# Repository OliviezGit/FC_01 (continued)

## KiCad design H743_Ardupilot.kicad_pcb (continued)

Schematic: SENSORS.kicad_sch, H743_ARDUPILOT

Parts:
C44, C45, C46: 4.7u; C_0402_1005Metric; MPN CL05A475MP5NRNC; DigiKey Part Number 1276-1482-1-ND
C47, C48, C49, C50, C51, C52: 100n X7R; C_0402_1005Metric; MPN CL05B104KO5NNNC; DigiKey Part Number 1276-1001-1-ND
C53, C54, C55, C56: 100n; C_0402_1005Metric; MPN CL05B104KO5NNNC; DigiKey Part Number 1276-1001-1-ND
J8: I2C1; SolderPadArray_1x04_P2.54mm_1x1mm; DigiKey Status Element PCB; aucun composant achete
J9: I2C_2; SolderPadArray_1x04_P2.54mm_1x1mm; DigiKey Status Element PCB; aucun composant achete
R34, R35, R36: 0R; R_0402_1005Metric; MPN RC0402JR-070RL; DigiKey Specs 0 Ω jumper, 0402 (1005), thick film
R37, R38: 4.7K; R_0402_1005Metric; MPN RC0402FR-074K7L; DigiKey Specs 4.7 kΩ ±1%, 0.063 W, 0402
U9: BMI088; BMI088_LGA16_4.5x3mm; MPN BMI088; DigiKey Specs 6-axis accel + gyro, I2C/SPI, LGA-16 4.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
U10: LSM6DSV16X; LSM6DSV16X_LGA14_3x2.5mm; MPN LSM6DSV16XTR; DigiKey Part Number 497-LSM6DSV16XTRCT-ND
U11: ICM-45686; TDK_ICM45686_LGA14_3x2.5mm; MPN ICM-45686; DigiKey Product ID 24374985
U12: BMP581; QFN10_BMP581_BOS; MPN BMP581; DigiKey Part Number 828-BMP581CT-ND
U13: DPS368XTSA1; Infineon_DPS368_PG-VLGA-8-2; MPN DPS368XTSA1; LCSC Part C3232508

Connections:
+3V3_MCU: C50.1, C51.1, C52.1, C53.1, C54.1, R37.1, R38.1, U9.11 (VDDIO), U10.5 (VDDIO), U11.5 (VDDIO), U12.1 (VDDIO), U13.2 (CSB), U13.6 (VDDIO); also elsewhere on the board
+3V3_SENS: C44.1, C45.1, C46.1, C47.1, C48.1, C49.1, C55.1, C56.1, U9.3 (VDD), U10.8 (VDD), U11.8 (VDD), U12.10 (VDD), U13.8 (VDD); also elsewhere on the board
+5V_SYS: J8.1, J9.1; also elsewhere on the board
/MCU/I2C1.SCL: J8.4; also elsewhere on the board
/MCU/I2C1.SDA: J8.3; also elsewhere on the board
/MCU/I2C2.SCL: J9.4, R37.2, U13.4 (SCL); also elsewhere on the board
/MCU/I2C2.SDA: J9.3, R38.2, U13.3 (SDA); also elsewhere on the board
/MCU/IMU1_CLKIN: R35.1; also elsewhere on the board
/MCU/IMU1_DRDY: R34.1; also elsewhere on the board
/MCU/IMU2_DRDY: R36.2; also elsewhere on the board
/MCU/IMU3_A_CS: U9.14 (~CSB1); also elsewhere on the board
/MCU/IMU3_G_CS: U9.5 (~CSB2); also elsewhere on the board
/MCU/SPI1.CS: U11.12 (CS); also elsewhere on the board
/MCU/SPI1.MISO: U11.1 (SDO/AD0); also elsewhere on the board
/MCU/SPI1.MOSI: U11.14 (SDI/SDIO/SDA); also elsewhere on the board
/MCU/SPI1.SCLK: U11.13 (SCLK/SCL); also elsewhere on the board
/MCU/SPI2.CS: U12.6 (CSB); also elsewhere on the board
/MCU/SPI2.MISO: U12.5 (SDO); also elsewhere on the board
/MCU/SPI2.MOSI: U12.4 (SDI); also elsewhere on the board
/MCU/SPI2.SCLK: U12.2 (SCK); also elsewhere on the board
/MCU/SPI3.MISO: U9.10 (SDO2), U9.15 (SDO1); also elsewhere on the board
/MCU/SPI3.MOSI: U9.9 (SDI/SDA); also elsewhere on the board
/MCU/SPI3.SCLK: U9.8 (SCK/SCL); also elsewhere on the board
/MCU/SPI4.CS: U10.12 (CS); also elsewhere on the board
/MCU/SPI4.MISO: U10.1 (SDO/SA0); also elsewhere on the board
/MCU/SPI4.MOSI: U10.14 (SDA); also elsewhere on the board
/MCU/SPI4.SCLK: U10.13 (SCL); also elsewhere on the board
GND: C44.2, C45.2, C46.2, C47.2, C48.2, C49.2, C50.2, C51.2, C52.2, C53.2, C54.2, C55.2, C56.2, J8.2, J9.2, U9.2 (GNDA), U9.4 (GNDA), U9.6 (GNDIO), U9.7 (PS), U10.2 (SDx/AH1/Qvar1), U10.3 (SCx/AH2/Qvar2), U10.6 (GND), U10.7 (GND), U11.6 (GND), U12.3 (VSS), U12.7 (INT), U12.8 (VSS), U12.9 (VSS), U13.1 (GND), U13.7 (GND); also elsewhere on the board
unnamed: R36.1, U10.4 (INT1)
unnamed: R34.2, U11.4 (INT1)
unnamed: R35.2, U11.9 (INT2/FSYNC/CLKIN)

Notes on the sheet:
I2C_1
I2C_2

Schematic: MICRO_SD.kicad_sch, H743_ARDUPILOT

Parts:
C57: 1u; C_0402_1005Metric; MPN CL05A105KA5NQNC; DigiKey Part Number 1276-1445-1-ND
C58: 100n; C_0402_1005Metric; MPN CL05B104KO5NNNC; DigiKey Part Number 1276-1001-1-ND
J12: 10067099-200LF; Amphenol_10067099-200LF_RevH; MPN 10067099-200LF; LCSC Part C5408015
R41, R42, R43, R44, R45, R46: 10K; R_0402_1005Metric; MPN RC0402FR-0710KL; DigiKey Specs 10K ±1%, 0402 (1005), thick film

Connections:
+3V3_MCU: C57.1, C58.1, J12.4 (VDD), R41.2, R42.2, R43.2, R44.2, R45.2, R46.2; also elsewhere on the board
/MCU/SDIO.CK: J12.5 (CLK), R41.1; also elsewhere on the board
/MCU/SDIO.CMD: J12.3 (CMD), R42.1; also elsewhere on the board
/MCU/SDIO.D0: J12.7 (DAT0), R43.1; also elsewhere on the board
/MCU/SDIO.D1: J12.8 (DAT1), R44.1; also elsewhere on the board
/MCU/SDIO.D2: J12.1 (DAT2), R45.1; also elsewhere on the board
/MCU/SDIO.D3: J12.2 (DAT3/CD), R46.1; also elsewhere on the board
GND: C57.2, C58.2, J12.6 (VSS), J12.9 (CD1), J12.10 (CD2); also elsewhere on the board

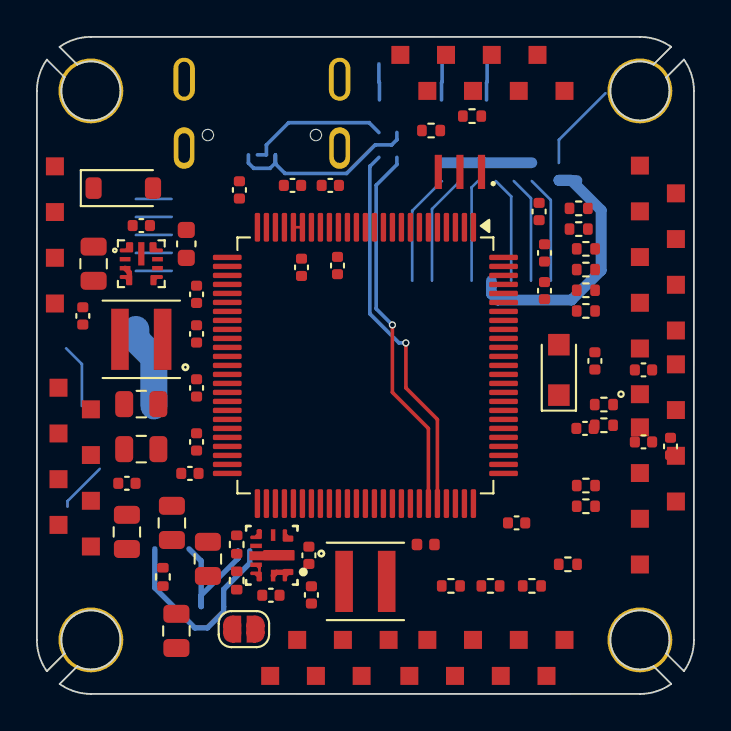
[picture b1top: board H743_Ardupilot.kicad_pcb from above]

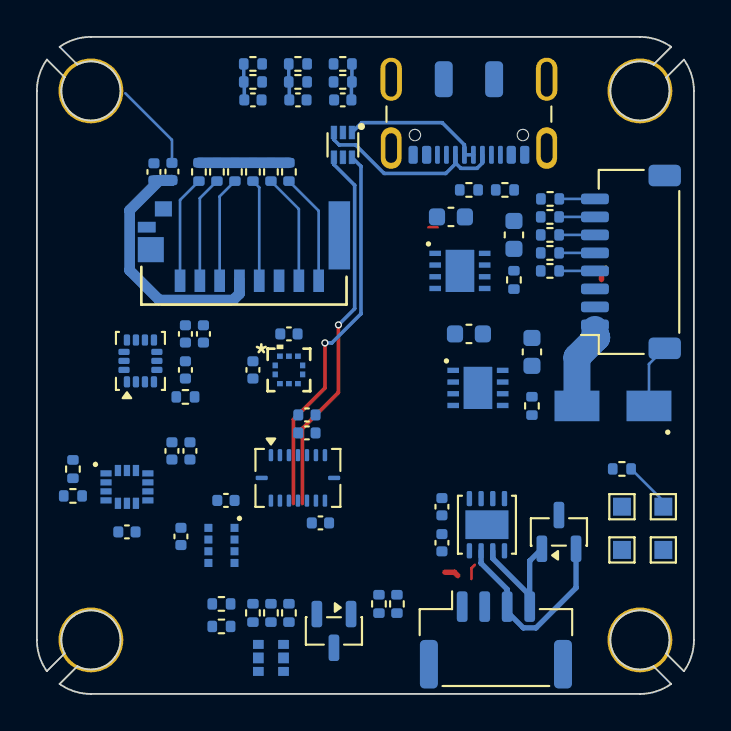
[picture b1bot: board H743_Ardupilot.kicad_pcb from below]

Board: 6 copper layers, 36.5 x 36.5 mm, 156 parts (77 on the bottom side), 123 nets.

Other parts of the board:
C18, C37: 10u; C_0805_2012Metric
C19, C22: 100n; C_0402_1005Metric
C26: 22u; C_0805_2012Metric
L2: 3.3u; L_Coilcraft_XGL4030
R8, R10: 100K; R_0402_1005Metric
R9: 16.5k; R_0402_1005Metric
R11: 12.4K; R_0402_1005Metric
U4: LMR604303SRAKRQ1; TI_RAK0009A_WQFN-HR-9_2.5x2.0mm

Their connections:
+9V: C26.1, C37.1, L2.2, R8.2, R10.2; also elsewhere on the board
/POWER/SW_9V: C22.2, L2.1, U4.3 (SW)
GND: C18.2, C19.2, C26.2, C37.2, R9.1, R11.2, U4.2 (PGND); also elsewhere on the board
unnamed: C22.1, U4.4 (BOOT)
unnamed: R10.1, R11.1, U4.6 (FB)
unnamed: R9.2, U4.7 (MODE/SYNC), U4.8 (RT)
unnamed: R8.1, U4.5 (PG)
VBAT: C18.1, C19.1, U4.1 (VIN), U4.9 (EN); also elsewhere on the board

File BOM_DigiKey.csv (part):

Sheet,Reference,Value,Manufacturer,MPN,Package,Footprint,Datasheet,DigiKey_Part_Number,DigiKey_URL,DigiKey_Specs,Unit_Price_EUR,Price_Qty,Price_Checked,DigiKey_Status,Footprint_Audit,Library_Audit,Supplier,Supplier_Order_Code,Supplier_URL
MCU.kicad_sch,C1,4.7u,Samsung Electro-Mechanics,CL05A475MP5NRNC,0402 (1005),Capacitor_SMD:C_0402_1005Metric,${KIPRJMOD}/composants/pdf/CL05A475MP5NRN.pdf,1276-1482-1-ND,https://www.digikey.fr/en/products/detail/samsung-electro-me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,"4.7 µF ±20%, 10 V, X5R, 0402",0.09,1,2026-09-27,Stock 0,Voir composants/catalogue.json et verification/REPORT.md,Voir composants/README.md,DigiKey France,1276-1482-1-ND,https://www.digikey.fr/en/products/detail/samsung-electro-me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
MCU.kicad_sch,C2,100n,Samsung Electro-Mechanics,CL05B104KO5NNNC,0402 (1005),Capacitor_SMD:C_0402_1005Metric,${KIPRJMOD}/composants/pdf/CL05B104KO5NNN.pdf,1276-1001-1-ND,https://www.digikey.fr/fr/products/detail/samsung-electro-me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,"100 nF ±10%, 16 V, X7R, 0402",0.09,1,2026-09-27,Stock 103052,Voir composants/catalogue.json et verification/REPORT.md,Voir composants/README.md,DigiKey France,1276-1001-1-ND,https://www.digikey.fr/fr/products/detail/samsung-electro-me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
MCU.kicad_sch,C3,100n,Samsung Electro-Mechanics,CL05B104KO5NNNC,0402 (1005),Capacitor_SMD:C_0402_1005Metric,${KIPRJMOD}/composants/pdf/CL05B104KO5NNN.pdf,1276-1001-1-ND,https://www.digikey.fr/fr/products/detail/samsung-electro-me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,"100 nF ±10%, 16 V, X7R, 0402",0.09,1,2026-09-27,Stock 103052,Voir composants/catalogue.json et verification/REPORT.md,Voir composants/README.md,DigiKey France,1276-1001-1-ND,https://www.digikey.fr/fr/products/detail/samsung-electro-me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
MCU.kicad_sch,C4,100n,Samsung Electro-Mechanics,CL05B104KO5NNNC,0402 (1005),Capacitor_SMD:C_0402_1005Metric,${KIPRJMOD}/composants/pdf/CL05B104KO5NNN.pdf,1276-1001-1-ND,https://www.digikey.fr/fr/products/detail/samsung-electro-me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,"100 nF ±10%, 16 V, X7R, 0402",0.09,1,2026-09-27,Stock 103052,Voir composants/catalogue.json et verification/REPORT.md,Voir composants/README.md,DigiKey France,1276-1001-1-ND,https://www.digikey.fr/fr/products/detail/samsung-electro-me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
MCU.kicad_sch,C5,100n,Samsung Electro-Mechanics,CL05B104KO5NNNC,0402 (1005),Capacitor_SMD:C_0402_1005Metric,${KIPRJMOD}/composants/pdf/CL05B104KO5NNN.pdf,1276-1001-1-ND,https://www.digikey.fr/fr/products/detail/samsung-electro-me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,"100 nF ±10%, 16 V, X7R, 0402",0.09,1,2026-09-27,Stock 103052,Voir composants/catalogue.json et verification/REPORT.md,Voir composants/README.md,DigiKey France,1276-1001-1-ND,https://www.digikey.fr/fr/products/detail/samsung-electro-me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
MCU.kicad_sch,C6,100n,Samsung Electro-Mechanics,CL05B104KO5NNNC,0402 (1005),Capacitor_SMD:C_0402_1005Metric,${KIPRJMOD}/composants/pdf/CL05B104KO5NNN.pdf,1276-1001-1-ND,https://www.digikey.fr/fr/products/detail/samsung-electro-me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,"100 nF ±10%, 16 V, X7R, 0402",0.09,1,2026-09-27,Stock 103052,Voir composants/catalogue.json et verification/REPORT.md,Voir composants/README.md,DigiKey France,1276-1001-1-ND,https://www.digikey.fr/fr/products/detail/samsung-electro-me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
MCU.kicad_sch,C7,2.2u,TDK,C1005X5R1C225M050BC,0402 (1005),Capacitor_SMD:C_0402_1005Metric,${KIPRJMOD}/composants/pdf/TDK_C.pdf,,,"2.2 µF ±20%, 16 V, X5R, 0402",0.104,10,2026-09-27,Voir composants/BOM_FR.csv,Voir composants/catalogue.json et verification/REPORT.md,Voir composants/README.md,Farnell France,2525017,https://fr.farnell.com/tdk/c1005x5r1c225m050bc/condensateur-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
MCU.kicad_sch,C8,100n,Samsung Electro-Mechanics,CL05B104KO5NNNC,0402 (1005),Capacitor_SMD:C_0402_1005Metric,${KIPRJMOD}/composants/pdf/CL05B104KO5NNN.pdf,1276-1001-1-ND,https://www.digikey.fr/fr/products/detail/samsung-electro-me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,"100 nF ±10%, 16 V, X7R, 0402",0.09,1,2026-09-27,Stock 103052,Voir composants/catalogue.json et verification/REPORT.md,Voir composants/README.md,DigiKey France,1276-1001-1-ND,https://www.digikey.fr/fr/products/detail/samsung-electro-me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
MCU.kicad_sch,C9,100n,Samsung Electro-Mechanics,CL05B104KO5NNNC,0402 (1005),Capacitor_SMD:C_0402_1005Metric,${KIPRJMOD}/composants/pdf/CL05B104KO5NNN.pdf,1276-1001-1-ND,https://www.digikey.fr/fr/products/detail/samsung-electro-me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,"100 nF ±10%, 16 V, X7R, 0402",0.09,1,2026-09-27,Stock 103052,Voir composants/catalogue.json et verification/REPORT.md,Voir composants/README.md,DigiKey France,1276-1001-1-ND,https://www.digikey.fr/fr/products/detail/samsung-electro-me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
MCU.kicad_sch,C10,2.2u,TDK,C1005X5R1C225M050BC,0402 (1005),Capacitor_SMD:C_0402_1005Metric,${KIPRJMOD}/composants/pdf/TDK_C.pdf,,,"2.2 µF ±20%, 16 V, X5R, 0402",0.104,10,2026-09-27,Voir composants/BOM_FR.csv,Voir composants/catalogue.json et verification/REPORT.md,Voir composants/README.md,Farnell France,2525017,https://fr.farnell.com/tdk/c1005x5r1c225m050bc/condensateur-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
MCU.kicad_sch,C11,100n,Samsung Electro-Mechanics,CL05B104KO5NNNC,0402 (1005),Capacitor_SMD:C_0402_1005Metric,${KIPRJMOD}/composants/pdf/CL05B104KO5NNN.pdf,1276-1001-1-ND,https://www.digikey.fr/fr/products/detail/samsung-electro-me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,"100 nF ±10%, 16 V, X7R, 0402",0.09,1,2026-09-27,Stock 103052,Voir composants/catalogue.json et verification/REPORT.md,Voir composants/README.md,DigiKey France,1276-1001-1-ND,https://www.digikey.fr/fr/products/detail/samsung-electro-me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
MCU.kicad_sch,C12,100n,Samsung Electro-Mechanics,CL05B104KO5NNNC,0402 (1005),Capacitor_SMD:C_0402_1005Metric,${KIPRJMOD}/composants/pdf/CL05B104KO5NNN.pdf,1276-1001-1-ND,https://www.digikey.fr/fr/products/detail/samsung-electro-me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,"100 nF ±10%, 16 V, X7R, 0402",0.09,1,2026-09-27,Stock 103052,Voir composants/catalogue.json et verification/REPORT.md,Voir composants/README.md,DigiKey France,1276-1001-1-ND,https://www.digikey.fr/fr/products/detail/samsung-electro-me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
MCU.kicad_sch,C14,1u,Samsung Electro-Mechanics,CL05A105KA5NQNC,0402 (1005),Capacitor_SMD:C_0402_1005Metric,${KIPRJMOD}/composants/pdf/CL05A105KA5NQN.pdf,1276-1445-1-ND,https://www.digikey.fr/fr/products/detail/samsung-electro-me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,"1 µF ±10%, 25 V, X5R, 0402",0.16,1,2026-09-27,Stock 2318576,Voir composants/catalogue.json et verification/REPORT.md,Voir composants/README.md,DigiKey France,1276-1445-1-ND,https://www.digikey.fr/fr/products/detail/samsung-electro-me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
MCU.kicad_sch,C15,100n,Samsung Electro-Mechanics,CL05B104KO5NNNC,0402 (1005),Capacitor_SMD:C_0402_1005Metric,${KIPRJMOD}/composants/pdf/CL05B104KO5NNN.pdf,1276-1001-1-ND,https://www.digikey.fr/fr/products/detail/samsung-electro-me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,"100 nF ±10%, 16 V, X7R, 0402",0.09,1,2026-09-27,Stock 103052,Voir composants/catalogue.json et verification/REPORT.md,Voir composants/README.md,DigiKey France,1276-1001-1-ND,https://www.digikey.fr/fr/products/detail/samsung-electro-me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
POWER.kicad_sch,C16,10u,Murata Electronics,GRM21BR61H106KE43L,0805 (2012),Capacitor_SMD:C_0805_2012Metric,${KIPRJMOD}/composants/pdf/GRM21.pdf,490-18663-1-ND,https://www.digikey.fr/en/products/detail/murata-electronics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,"10 µF ±10%, 50 V, X5R, 0805",0.28,1,2026-09-27,Stock 0,Voir composants/catalogue.json et verification/REPORT.md,Voir composants/README.md,DigiKey France,490-18663-1-ND,https://www.digikey.fr/en/products/detail/murata-electronics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
POWER.kicad_sch,C17,100n,Murata Electronics,GCM155R71H104KE02D,0402 (1005 Metric),Capacitor_SMD:C_0402_1005Metric,${KIPRJMOD}/composants/pdf/GCM155.pdf,490-10672-1-ND,https://www.digikey.fr/fr/products/detail/murata-electronics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,"100 nF ±10%, 50 V, X7R, 0402 (1005)",0.09,1,2026-09-27,Stock 16172272,Voir composants/catalogue.json et verification/REPORT.md,Voir composants/README.md,DigiKey France,490-10672-1-ND,https://www.digikey.fr/fr/products/detail/murata-electronics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
POWER.kicad_sch,C18,10u,Murata Electronics,GRM21BR61H106KE43L,0805 (2012),Capacitor_SMD:C_0805_2012Metric,${KIPRJMOD}/composants/pdf/GRM21.pdf,490-18663-1-ND,https://www.digikey.fr/en/products/detail/murata-electronics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,"10 µF ±10%, 50 V, X5R, 0805",0.28,1,2026-09-27,Stock 0,Voir composants/catalogue.json et verification/REPORT.md,Voir composants/README.md,DigiKey France,490-18663-1-ND,https://www.digikey.fr/en/products/detail/murata-electronics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

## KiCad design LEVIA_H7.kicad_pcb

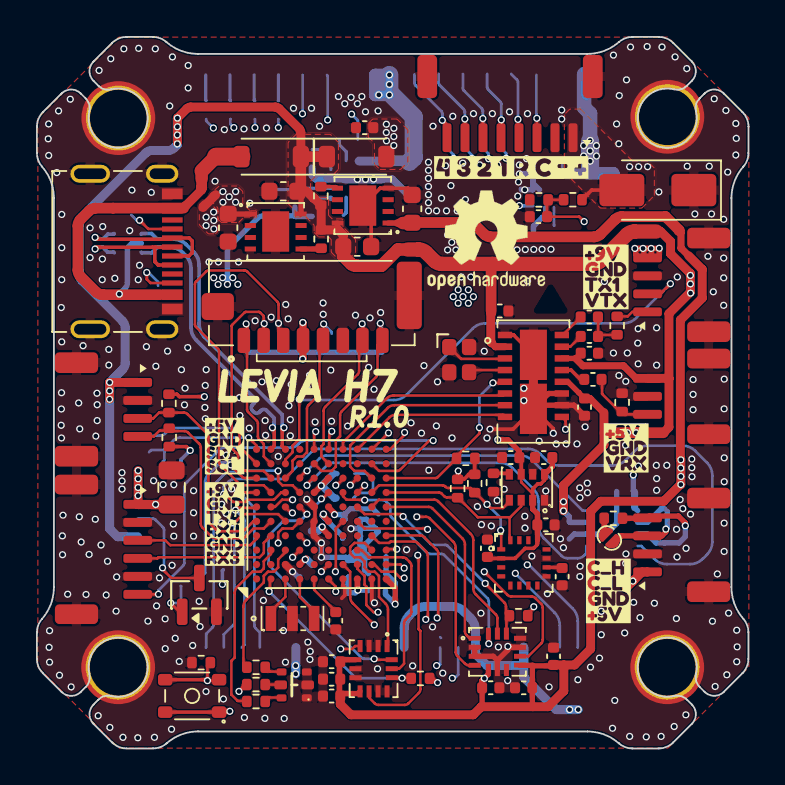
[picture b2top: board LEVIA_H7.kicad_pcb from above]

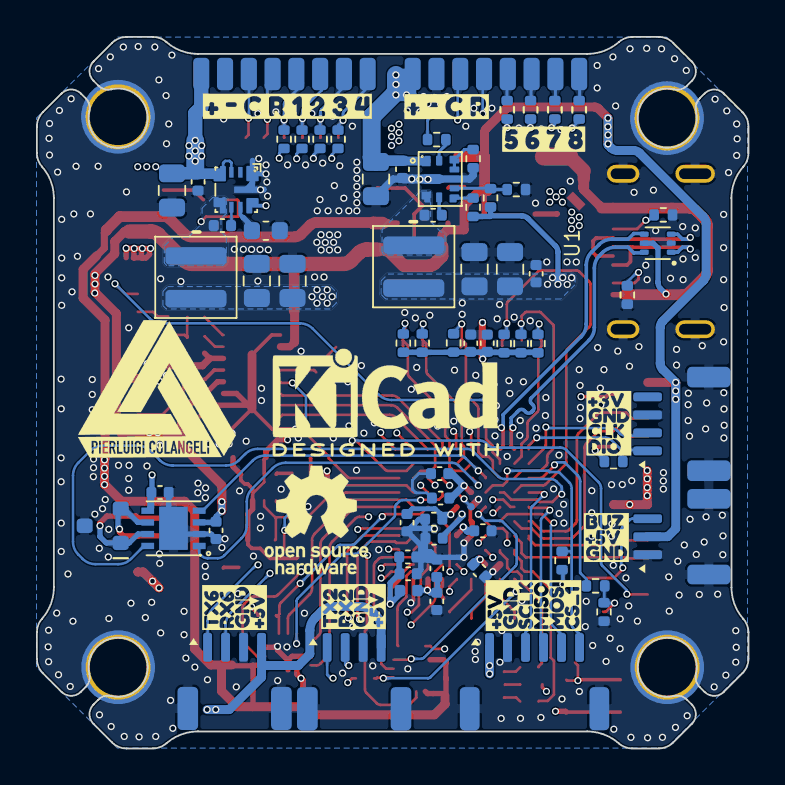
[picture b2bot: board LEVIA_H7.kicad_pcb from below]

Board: 6 copper layers, 39.5 x 39.5 mm, 170 parts (90 on the bottom side), 119 nets.

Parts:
C1, C4, C5, C6, C9, C10, C15, C16, C17, C20, C21, C26, C28, C33, C34, C35, C38, C39, C40, C43, C44, C47, C48, C49, C50, C54: 100n; C_0402_1005Metric
C2, C12, C41, C42, C51: 4.7u; C_0402_1005Metric
C3, C7, C53: 1u; C_0402_1005Metric
C8, C11: 2.2u; C_0402_1005Metric
C13, C14: 10u; C_0805_2012Metric
C18: 1u; C_0603_1608Metric
C22, C24, C25, C27, C52: 22u; C_0805_2012Metric
C29, C30, C31, C32: 4.7u; C_0603_1608Metric
C36, C37: 10u; C_0402_1005Metric
C45, C46: 10n; C_0402_1005Metric
D1: LED_RGB_EP; LED-ARRAY-SMD_6P-L1.6-W1.6-TL
D2: SMAJ30CA; D_SMA
D3, D4: 1N5819WL; D_SOD-123
D6: PESD2CAN; SOT-23
FB1: 600Ω@100MHz; L_0402_1005Metric
H1, H2, H3, H4: MountingHole_Pad; MountingHole_3.2mm_M3_ISO14580_Pad_TopBottom
J1: TF-028-H265; TF-SMD_TF-021B-H265
JP1: SolderJumper_2_Open; SolderJumper_Mini
L1, L2: 2.2u; L_Coilcraft_XAL4030-XXX
NT1: NetTie_2; NetTie-2_SMD_Pad0.5mm
Q1: AO3400A; SOT-23
R1, R2: 5.1K; R_0402_1005Metric
R3, R8, R10, R19, R20, R21, R27, R28, R32, R35, R36, R37, R38, R39, R40, R41: 10K; R_0402_1005Metric
R4, R5, R6: 220R; R_0402_1005Metric
R7, R9, R15, R29: 100K; R_0402_1005Metric
R11, R34: 1K; R_0402_1005Metric
R12: 16.5k; R_0402_1005Metric
R16: 12.4K; R_0402_1005Metric
R22, R23: 75R; R_0402_1005Metric
R24: 120R; R_0402_1005Metric
R25, R26, R30, R31: 4.7K; R_0402_1005Metric
R42, R43, R44, R45, R46, R47, R48, R49: 10R; R_0402_1005Metric
SW2: RKCGG140SMTRLFS; SW-SMD_4P-L3.0-W2.6-P1.80-LS3.5
TP3, TP4, TP5, TP6, TP7, TP8, TP9, TP10, TP12, TP13, TP14, TP15, TP16, TP17, TP18, TP19: TestPoint_Pad_1.8x0.9mm
TP11: TestPoint; TestPoint_Pad_D1.0mm
U1: USBLC6-2P6; SOT-666-6_L1.6-W1.2-P0.50-LS1.6-BL
U2: STM32H743VIHx; TFBGA-100_8x8mm_Layout10x10_P0.8mm
U3, U8, U10, U13, U18, U24: ZX-SH1.0-4PWT; CONN-SMD_4P-P1.00_MEGASTAR_ZX-SH1.0-4PWT
U4: LMR43620R5RPER; VQFN-9_L2.1-W2.1-P0.50-TL
U5: LMR604303SRAKRQ1; WQFN-9_L2.5-W2.0_RAK0009A
U6, U7: AP7361C-33FGE-7; DFN-8_L3.0-W3.0-P0.65-BL-EP
U9: AT7456ELAH; LGA-16_L6.8-W4.0-P0.65-TL-2EP
U11, U21: ZX-SH1.0-3PWT; CONN-SMD_3P-P1.00_MEGASTAR_ZX-SH1.0-3PWT
U12: SIT1051TK/3; HVSON-8_L3.0-W3.0-P0.65-BL-EP
U14, U15: ICM-42688-P; LGA-14_L3.0-W2.5-P0.50-TL
U16: DPS368XTSA1; LGA-8_L2.5-W2.0-P0.65-TR_DPS368
U17: IST8310; LGA-16_L3.0-W3.0-P0.50-BL_SQ
U19, U20: ZX-SH1.0-6PWT; CONN-SMD_6P-P1.00_MEGASTAR_ZX-SH1.0-6PWT
U22: ZX-SH1.0-8PWT; CONN-SMD_8P-P1.00_MEGASTAR_ZX-SH1.0-8PWT
USB1: HC-TYPE-C-16P-01M; USB-C-SMD_HCTL_HC-TYPE-C-16P-01M
Y1: 8MHz; OSC-SMD_3P-L3.2-W1.3-P1.20-L
Y2: XL7EL89COI-111YLC-27M; Crystal_SMD_2016-4Pin_2.0x1.6mm
kibuzzard-6A40F4B5: G***; kibuzzard-6A40F4B5
kibuzzard-6A40F5CA: G***; kibuzzard-6A40F5CA
kibuzzard-6A40F8CE: G***; kibuzzard-6A40F8CE
kibuzzard-6A40F9B9: G***; kibuzzard-6A40F9B9
kibuzzard-6A40F45A: G***; kibuzzard-6A40F45A
kibuzzard-6A40F56A: G***; kibuzzard-6A40F56A
kibuzzard-6A40F62C: G***; kibuzzard-6A40F62C
kibuzzard-6A40F422: G***; kibuzzard-6A40F422
kibuzzard-6A40F649: G***; kibuzzard-6A40F649
kibuzzard-6A40F691: G***; kibuzzard-6A40F691
kibuzzard-6A40F712: G***; kibuzzard-6A40F712
kibuzzard-6A40F981: G***; kibuzzard-6A40F981
kibuzzard-6A4131D0: G***; kibuzzard-6A4131D0
kibuzzard-6A4131DD: G***; kibuzzard-6A4131DD

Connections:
+3V3_MCU: C31.1, C39.1, C53.1, C54.1, J1.4 (VDD), NT1.1, R5.2, R7.1, R21.2, R25.1, R26.1, R27.1, R28.1, R30.1, R31.1, R32.1, R36.2, R37.2, R38.2, R39.2, R40.2, R41.2, SW2.1, SW2.2, U6.1 (OUT), U12.5 (VIO)
+3V3_SENS: C32.1, C41.1, C42.1, C43.1, C44.1, C45.1, C46.1, C47.1, C48.1, C49.1, C50.1, U7.1 (OUT), U14.5 (VDDIO), U14.8 (VDD), U15.5 (VDDIO), U15.8 (VDD), U16.2 (CSB), U16.6 (VDDIO), U16.8 (VDD), U17.2 (VDD), U17.13 (VDDIO)
+5V: C22.1, C24.1, C26.1, D3.2 (A), L1.2, U4.8 (VOUT/FB)
+5V_SYS: C29.1, C30.1, C33.1, C34.1, C35.1, C40.1, D3.1 (K), D4.1 (K), R19.2, R20.2, U6.8 (IN), U7.8 (IN), U8.4, U9.2 (DVDD), U9.9 (~RESET), U9.12 (AVDD), U9.14 (PVDD), U11.3, U12.3 (VCC), U13.1, U18.1, U19.1, U21.2, U24.4
+9V: C25.1, C27.1, C28.1, C52.1, L2.2, R9.2, R15.2, U10.4, U20.1
/ANALOG VTX/SPI2.CS: R21.1, U2.K8 (PB12), U9.5 (~CS)
/ANALOG VTX/SPI2.MISO: U2.H10 (PB14), U9.8 (SDOUT)
/ANALOG VTX/SPI2.MOSI: U2.G10 (PB15), U9.6 (SDIN)
/ANALOG VTX/SPI2.SCLK: U2.J8 (PB13), U9.7 (SCLK)
/ANALOG VTX/UART1.TX: U2.C9 (PA9), U10.2
/ANALOG VTX/VRX: C38.2, R23.1, U11.1
/ANALOG VTX/VTX: R22.2, U10.1
/BUZZER/BUZZER: R34.1, U2.A8 (PA15)
/BUZZER/BUZZ_PAD-: Q1.3 (D), U21.3
/CAN/CAN1.RX: U2.D8 (PD0), U12.4 (RXD)
/CAN/CAN1.SILENT: U2.C7 (PD3), U12.8 (S)
/CAN/CAN1.TX: U2.E8 (PD1), U12.1 (TXD)
/CAN/CAN1_H: D6.1 (A1), R24.1, U12.7 (CANH), U13.4
/CAN/CAN1_L: D6.2 (A2), JP1.1 (A), U12.6 (CANL), U13.3
/DIGITAL VTX/UART3.RX: U2.J9 (PD9), U20.6
/DIGITAL VTX/UART4.RX: U2.B4 (PB8), U20.4
/DIGITAL VTX/UART4.TX: U2.A4 (PB9), U20.3
/I2C1|SPI3/I2C1.SCL: R30.2, U2.B5 (PB6), U18.4
/I2C1|SPI3/I2C1.SDA: R31.2, U2.A5 (PB7), U18.3
/I2C1|SPI3/SPI3.CS1: R32.2, U2.D7 (PD4), U19.6
/I2C1|SPI3/SPI3.MISO: U2.A6 (PB4), U19.4
/I2C1|SPI3/SPI3.MOSI: U2.C5 (PB5), U19.5
/I2C1|SPI3/SPI3.SCLK: U2.A7 (PB3), U19.3
/MCU/9V_EN: R8.1, U2.D3 (PE5)
/MCU/ADC1_CURR1: TP3.1 (1_1), U2.F2 (PC1), U22.3
/MCU/ADC1_CURR2: TP19.1 (1_1), U2.K3 (PA7)
/MCU/ADC1_VBAT1: C17.1, R10.2, R11.1, U2.F1 (PC0)
/MCU/BOOT0: R3.1, SW2.3, SW2.4, U2.D5 (BOOT0)
/MCU/GYRO1_CLKIN: U2.H8 (PD14), U14.9 (CLKIN)
/MCU/GYRO1_EXTI: U2.G5 (PB2), U14.4 (INT1)
/MCU/GYRO2_CLKIN: U2.G8 (PD15), U15.9 (CLKIN)
/MCU/GYRO2_EXTI: U2.H7 (PE15), U15.4 (INT1)
/MCU/I2C2.SCL: R25.2, U2.J7 (PB10), U16.4 (SCL), U17.1 (SCL)
/MCU/I2C2.SDA: R26.2, U2.K7 (PB11), U16.3 (SDA), U17.16 (SDA)
/MCU/LED0: R4.2, U2.B3 (PE3)
/MCU/LED1: R6.2, U2.C3 (PE4)
/MCU/MOTOR1: R42.1, U2.J4 (PB0)
/MCU/MOTOR2: R43.1, U2.K4 (PB1)
/MCU/MOTOR3: R44.1, U2.G2 (PA0)
/MCU/MOTOR4: R45.1, U2.H2 (PA1)
/MCU/MOTOR5: R46.1, U2.J2 (PA2)
/MCU/MOTOR6: R47.1, U2.K2 (PA3)
/MCU/MOTOR7: R48.1, U2.K10 (PD12)
/MCU/MOTOR8: R49.1, U2.J10 (PD13)
/MCU/NRST: C1.1, U2.E1 (NRST)
/MCU/OSC_IN: U2.C1 (PH0), Y1.1
/MCU/OSC_OUT: U2.D1 (PH1), Y1.3
/MCU/SDIO.CK: J1.5 (CLK), R36.1, U2.C8 (PC12)
/MCU/SDIO.CMD: J1.3 (CMD), R37.1, U2.B7 (PD2)
/MCU/SDIO.D0: J1.7 (DAT0), R38.1, U2.F9 (PC8)
/MCU/SDIO.D1: J1.8 (DAT1), R39.1, U2.E9 (PC9)
/MCU/SDIO.D2: J1.1 (DAT2), R40.1, U2.B9 (PC10)
/MCU/SDIO.D3: J1.2 (DAT3/CD), R41.1, U2.B8 (PC11)
/MCU/SPI1.CS: R27.2, U2.B1 (PC15), U14.12 (CS)
/MCU/SPI1.MISO: U2.J3 (PA6), U14.1 (SDO)
/MCU/SPI1.MOSI: U2.D6 (PD7), U14.14 (SDI)
/MCU/SPI1.SCLK: U2.H3 (PA5), U14.13 (SCLK)
/MCU/SPI4.CS: R28.2, U2.H6 (PE11), U15.12 (CS)
/MCU/SPI4.MISO: U2.K6 (PE13), U15.1 (SDO)
/MCU/SPI4.MOSI: U2.G7 (PE14), U15.14 (SDI)
/MCU/SPI4.SCLK: U2.J6 (PE12), U15.13 (SCLK)
/MCU/SWCLK: U2.A9 (PA14), U3.2
/MCU/SWDIO: R7.2, U2.A10 (PA13), U3.1
/MCU/UART2.RX: U2.C6 (PD6), U24.2
/MCU/UART2.TX: U2.B6 (PD5), U24.1
/MCU/UART6.RX: U2.E10 (PC7), U8.2
/MCU/UART6.TX: U2.F10 (PC6), U8.1
/MCU/UART7.RX: TP18.1 (1_1), U2.H5 (PE7)
/MCU/UART8.RX: TP4.1 (1_1), U2.D4 (PE0), U22.4
/MCU/USB_OTG_P.DN: U1.4 (I/O2), U2.C10 (PA11)
/MCU/USB_OTG_P.DP: U1.6 (I/O1), U2.B10 (PA12)
/MCU/VDD: C2.1, C4.1, C6.1, C7.1, C9.1, C10.1, C12.1, FB1.1, NT1.2, U2.D2 (VDD), U2.F4 (VDDLDO), U2.F5 (VDD), U2.F6 (VDD33_USB), U2.K1 (VDD)
/MCU/VDDA: C3.1, C5.1, FB1.2, U2.H1 (VDDA)
/MOTORS[1-4]/S1: R42.2, TP5.1 (1_1), U22.5
/MOTORS[1-4]/S2: R43.2, TP6.1 (1_1), U22.6
/MOTORS[1-4]/S3: R44.2, TP7.1 (1_1), U22.7
/MOTORS[1-4]/S4: R45.2, TP8.1 (1_1), U22.8
/MOTORS[5-8]/S5: R46.2, TP12.1 (1_1)
/MOTORS[5-8]/S6: R47.2, TP13.1 (1_1)
/MOTORS[5-8]/S7: R48.2, TP14.1 (1_1)
/MOTORS[5-8]/S8: R49.2, TP15.1 (1_1)
/POWER/DJI_EN: R8.2, U5.9 (EN)
/POWER/SW_5V: C20.2, L1.1, U4.5 (SW)
/POWER/SW_9V: C21.2, L2.1, U5.3 (SW)
/USB_OTG.DN: U1.3 (I/O2), USB1.A7 (D-), USB1.B7 (D-)
/USB_OTG.DP: U1.1 (I/O1), USB1.A6 (D+), USB1.B6 (D+)
GND: C1.2, C2.2, C3.2, C4.2, C5.2, C6.2, C7.2, C8.2, C9.2, C10.2, C11.2, C12.2, C13.2, C14.2, C15.2, C16.2, C17.2, C18.2, C22.2, C24.2, C25.2, C26.2, C27.2, C28.2, C29.2, C30.2, C31.2, C32.2, C33.2, C34.2, C35.2, C39.2, C40.2, C41.2, C42.2, C43.2, C44.2, C45.2, C46.2, C47.2, C48.2, C49.2, C50.2, C51.2, C52.2, C53.2, C54.2, D1.1 (RK), D1.2 (GK), D1.3 (BK), D2.1 (A1), D6.3 (Com), H1.1 (1_1), H2.1 (1_1), H3.1 (1_1), H4.1 (1_1), J1.6 (VSS), J1.9 (SH), J1.10 (SH), Q1.2 (S), R1.2, R2.2, R3.2, R11.2, R12.1, R16.2, R23.2, R29.1, R35.2, TP10.1 (1_1), TP17.1 (1_1), U1.2 (GND), U2.C2 (VSS), U2.E4 (VSS), U2.E5 (VSS), U2.E6 (VSS), U2.G1 (VSSA), U2.J1 (VSS), U3.3, U3.5, U3.6, U4.1 (RT), U4.9 (GND), U5.2 (PGND), U6.4 (GND), U6.9 (EXP), U7.4 (GND), U7.9 (EXP), U8.3, U8.5, U8.6, U9.1 (DGND), U9.10 (AGND), U9.11 (PGND), U9.17 (EP1), U9.18 (EP2), U10.3, U10.5, U10.6, U11.2, U11.4, U11.5, U12.2 (GND), U12.9 (EP), U13.2, U13.5, U13.6, U14.2 (RESV), U14.3 (RESV), U14.6 (GND), U14.7 (RESV), U14.10 (RESV), U14.11 (RESV), U15.2 (RESV), U15.3 (RESV), U15.6 (GND), U15.7 (RESV), U15.10 (RESV), U15.11 (RESV), U16.1 (GND), U16.7 (GND), U17.9 (GND), U17.11 (GND), U18.2, U18.5, U18.6, U19.2, U19.7, U19.8, U20.2, U20.5, U20.7, U20.8, U21.1, U21.4, U21.5, U22.2, U22.9, U22.10, U24.3, U24.5, U24.6, USB1.25 (SHIELD), USB1.26 (SHIELD), USB1.27 (SHIELD), USB1.28 (SHIELD), USB1.A1 (GND), USB1.A12 (GND), USB1.B1 (GND), USB1.B12 (GND), Y1.2, Y2.2 (G), Y2.4 (G)
unnamed: C36.2, C37.2, R22.1
unnamed: D1.4 (BA), R4.1
unnamed: D1.5 (GA), R5.1
unnamed: D1.6 (RA), R6.1
unnamed: JP1.2 (B), R24.2
unnamed: Q1.1 (G), R34.2, R35.1
unnamed: TP11.1 (1_1), U2.F7 (PDR_ON)
unnamed: C20.1, U4.6 (BOOT)
unnamed: C18.1, U4.7 (VCC)
unnamed: C21.1, U5.4 (BOOT)
unnamed: R15.1, R16.1, U5.6 (FB)
unnamed: R12.2, U5.7 (MODE/SYNC), U5.8 (RT)
unnamed: R9.1, U5.5 (PG)
unnamed: R19.1, U6.5 (EN)
unnamed: R20.1, U7.5 (EN)
unnamed: U9.3 (CLKIN), Y2.1
unnamed: C37.1, U9.15 (SAG)
unnamed: C38.1, U9.13 (VIN)
unnamed: C36.1, U9.16 (VOUT)
unnamed: U9.4 (XFB), Y2.3
unnamed: R29.2, U16.5 (SDO)
unnamed: C51.1, U17.10 (C1)
unnamed: R1.1, USB1.A5 (CC1)
unnamed: R2.1, USB1.B5 (CC2)
VBAT: C13.1, C14.1, C15.1, C16.1, D2.2 (A2), R10.1, TP9.1 (1_1), TP16.1 (1_1), U4.3 (EN/UVLO), U4.4 (VIN), U5.1 (VIN), U22.1
VBUS: D4.2 (A), U1.5 (VBUS), USB1.A4 (VBUS), USB1.A9 (VBUS), USB1.B4 (VBUS), USB1.B9 (VBUS)
VCAP: C8.1, C11.1, U2.E7 (VCAP), U2.F8 (VCAP)
